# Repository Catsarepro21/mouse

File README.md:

# Mouse

A custom Bluetooth mouse with a printed case, a PMW3360 optical sensor, and RGB lighting. The shape is based on the Lenovo Yoga Bluetooth Silent Mouse, with a rounded back for a comfortable palm grip.

## Why I made it

My current mouse feels a bit small, and I really liked the shape and click feel of a Lenovo Yoga mouse I used before. I wanted to make my own mouse with that kind of comfort, while learning how to put the PCB, firmware, and case together. I also wanted RGB lighting with diffusers built into the sides.

## The design

- Seeed XIAO ESP32-C3 for Bluetooth and battery charging
- PMW3360 sensor with an LM19-LSI lens
- Left click, right click, and a clickable scroll wheel
- Seven addressable RGB LEDs, including one near the wheel
- A printed top cover, base, wheel, battery tray, and two translucent side diffusers
- A rear USB-C opening and adhesive PTFE skates

The mouse sends input over Bluetooth. USB is used for charging and flashing the firmware.

## CAD assembly

The exploded view shows the case, PCB, battery envelope, and removable tray. The battery and rear USB-C connector in the model are references for checking the layout.

The assembly STEP file is in `cad/mouse.step`. The Onshape document also has views of the PCB, the assembled mouse, and the individual case parts. [Open the Onshape assembly](https://cad.onshape.com/documents/f339b248a5d93d00b356f41b/w/cae739c57158e79859cbe66f/e/194018f47ffd620b1df57684).

## PCB

The PCB carries the controller, sensor, switches, scroll encoder, battery connector, and LEDs.

## Schematic

## Files

| Folder | Contents |
| --- | --- |
| `production/firmware` | Compiled firmware for the XIAO ESP32-C3 |
| `production/print` | STL files for the case, wheel, tray, and diffusers |
| `production/gerbers.zip` | Copper, mask, silkscreen, outline, and drill files |
| `PCB` | KiCad project, schematic, PCB, custom footprints, and component models |
| `code` | Arduino source and the sensor SROM header |
| `cad` | Full assembly STEP file and skate patterns |

## Firmware and use

I edit the firmware in IntelliJ IDEA and build it with Arduino CLI. It handles Bluetooth mouse reports, the three buttons, scroll input, RGB lighting, and the PMW3360 sensor.

With Arduino CLI installed, run these from the repository folder to install the board support and libraries, then compile.

```powershell
arduino-cli config add board_manager.additional_urls https://espressif.github.io/arduino-esp32/package_esp32_index.json
arduino-cli core update-index
arduino-cli core install esp32:esp32@3.3.12
arduino-cli lib install "HijelHID_BLEMouse@0.1.0" "NimBLE-Arduino@2.5.2" "Adafruit NeoPixel@1.15.5"
arduino-cli compile --fqbn esp32:esp32:XIAO_ESP32C3 code
```

After uploading the firmware to the assembled mouse, pair with **Seashell Mouse** in the computer's Bluetooth settings. The compiled image in `production/firmware` is a merged flash image for address `0x0`.

The PMW3360 SROM was adapted from the header in [macsboost/pmw3360](https://github.com/macsboost/pmw3360/blob/master/PMW3360_SROM.h).

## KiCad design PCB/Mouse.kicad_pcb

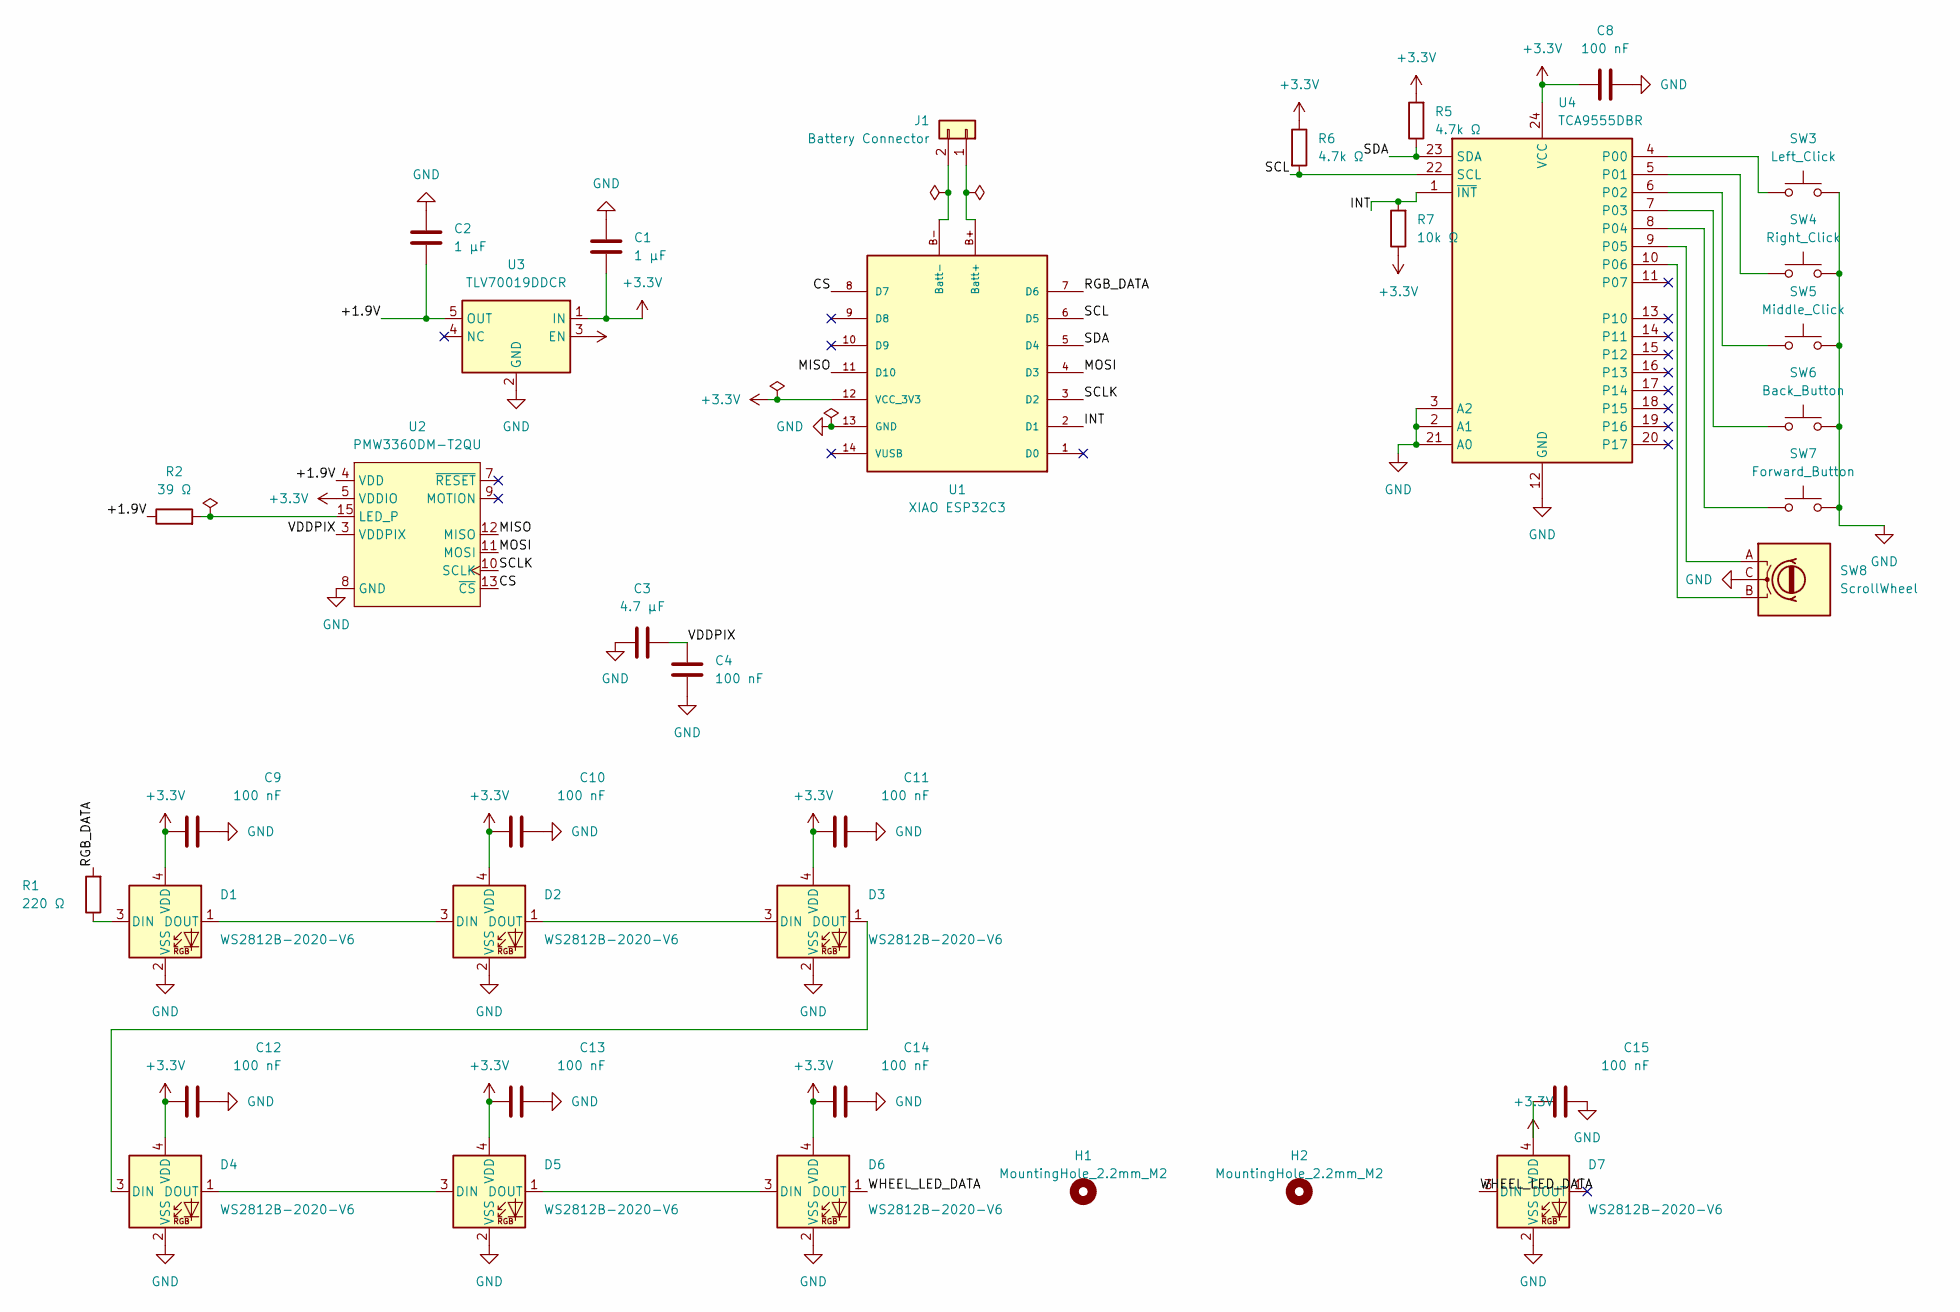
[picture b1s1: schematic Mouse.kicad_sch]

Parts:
C1, C2: 1 µF; C_0603_1608Metric_Pad1.08x0.95mm_HandSolder
C3: 4.7 µF; C_0805_2012Metric_Pad1.18x1.45mm_HandSolder
C4, C8, C9, C10, C11, C12, C13, C14, C15: 100 nF; C_0603_1608Metric_Pad1.08x0.95mm_HandSolder
D1, D2, D3, D4, D5, D6, D7: WS2812B-2020-V6; LED_WS2812B-2020_PLCC4_2.0x2.0mm
H1, H2: MountingHole_2.2mm_M2
J1: Battery Connector; JST_PH_S2B-PH-SM4-TB_1x02-1MP_P2.00mm_Horizontal
R1: 220 Ω; R_0603_1608Metric_Pad0.98x0.95mm_HandSolder
R2: 39 Ω; R_0603_1608Metric_Pad0.98x0.95mm_HandSolder
R5, R6: 4.7k Ω; R_0603_1608Metric_Pad0.98x0.95mm_HandSolder
R7: 10k Ω; R_0603_1608Metric_Pad0.98x0.95mm_HandSolder
SW3: Left_Click; Kailh_CMI627301D07
SW4: Right_Click; Kailh_CMI627301D07
SW5: Middle_Click; Kailh_CMI627301D07
SW6: Back_Button; SW_SPST_EVQP7A
SW7: Forward_Button; SW_SPST_EVQP7A
SW8: ScrollWheel; RotaryEncoder_Alps_EC10E1220501
U1: XIAO ESP32C3; xiao_esp32c3
U2: PMW3360DM-T2QU; PMW3360DM-T2QU 16Pin
U3: TLV70019DDCR; TI_DDC0005A
U4: TCA9555DBR; SSOP-24_5.3x8.2mm_P0.65mm

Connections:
+3.3V: C1.2, C8.1, C9.1, C10.1, C11.1, C12.1, C13.1, C14.1, C15.1, D1.4 (VDD), D2.4 (VDD), D3.4 (VDD), D4.4 (VDD), D5.4 (VDD), D6.4 (VDD), D7.4 (VDD), R5.2, R6.1, R7.1, U1.12 (VCC_3V3), U2.5 (VDDIO), U3.1 (IN), U3.3 (EN), U4.24 (VCC)
/+1.9V: C2.2, R2.1, U2.4 (VDD), U3.5 (OUT)
/CS: U1.8 (D7), U2.13 (~CS)
/INT: R7.2, U1.2 (D1), U4.1 (~INT)
/MISO: U1.11 (D10), U2.12 (MISO)
/MOSI: U1.4 (D3), U2.11 (MOSI)
/RGB_DATA: R1.2, U1.7 (D6)
/SCL: R6.2, U1.6 (D5), U4.22 (SCL)
/SCLK: U1.3 (D2), U2.10 (SCLK)
/SDA: R5.1, U1.5 (D4), U4.23 (SDA)
/VDDPIX: C3.1, C4.1, U2.3 (VDDPIX)
/WHEEL_LED_DATA: D6.1 (DOUT), D7.3 (DIN)
GND: C1.1, C2.1, C3.2, C4.2, C8.2, C9.2, C10.2, C11.2, C12.2, C13.2, C14.2, C15.2, D1.2 (VSS), D2.2 (VSS), D3.2 (VSS), D4.2 (VSS), D5.2 (VSS), D6.2 (VSS), D7.2 (VSS), SW3.2, SW4.2, SW5.2, SW6.2, SW7.2, SW8.C, U1.13 (GND), U2.8 (GND), U3.2 (GND), U4.2 (A1), U4.3 (A2), U4.12 (GND), U4.21 (A0)
unnamed: D1.3 (DIN), R1.1
unnamed: D1.1 (DOUT), D2.3 (DIN)
unnamed: D2.1 (DOUT), D3.3 (DIN)
unnamed: D3.1 (DOUT), D4.3 (DIN)
unnamed: D4.1 (DOUT), D5.3 (DIN)
unnamed: D5.1 (DOUT), D6.3 (DIN)
unnamed: J1.1, U1.B+ (Batt+)
unnamed: J1.2, U1.B- (Batt-)
unnamed: R2.2, U2.15 (LED_P)
unnamed: SW3.1, U4.4 (P00)
unnamed: SW4.1, U4.5 (P01)
unnamed: SW5.1, U4.6 (P02)
unnamed: SW6.1, U4.7 (P03)
unnamed: SW7.1, U4.8 (P04)
unnamed: SW8.A, U4.9 (P05)
unnamed: SW8.B, U4.10 (P06)

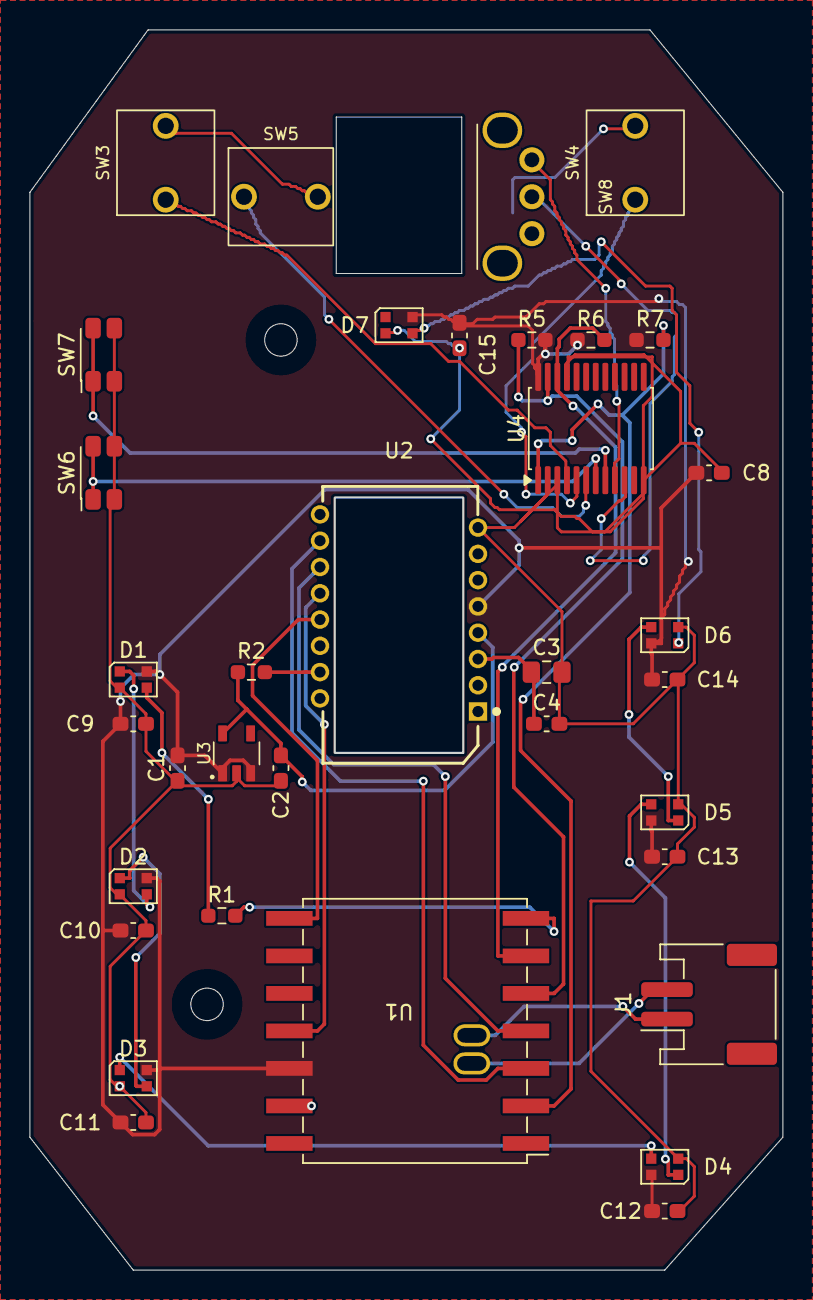
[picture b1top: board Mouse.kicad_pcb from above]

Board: 2 copper layers, 51.0 x 84.0 mm, 37 parts (0 on the bottom side), 29 nets.
